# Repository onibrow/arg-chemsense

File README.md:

# Arias Reesearch Group - Chemical Sensors

Quad Channel Differential Potentiometric Sensor

Using the MCP3424 to sense differential voltage - firmware library [here](https://github.com/battosai30/MCP3424)

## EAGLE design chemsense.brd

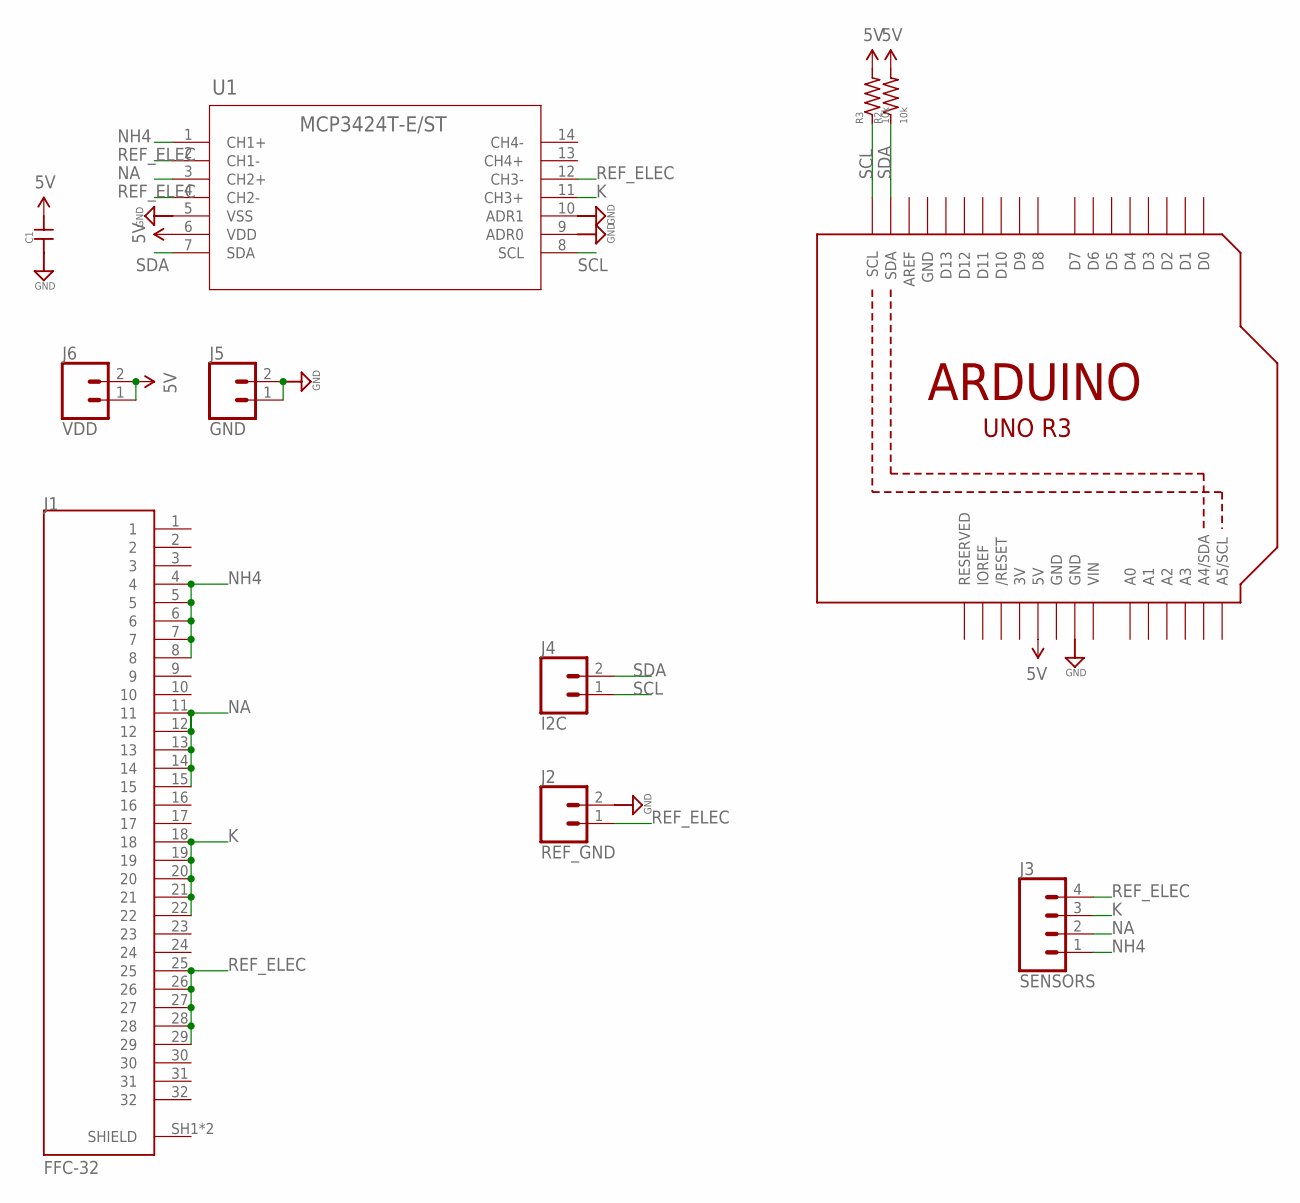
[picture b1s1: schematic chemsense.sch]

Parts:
C1: CAP0603-CAP; 0603-CAP
J1: FFC-32; MOLEX_503480-3200
J2: REF_GND; 1X02
J3: SENSORS; 1X04
J4: I2C; 1X02
J5: GND; 1X02
J6: VDD; 1X02
M1: ARDUINO_R3_ICSP; ARDUINOR3_ICSP
R2, R3: 10k; 0603-RES
U1: MCP3424T-E/ST; TSSOP14_MC

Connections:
3V: M1.3V
5V: C1.2, J6.1, J6.2, M1.5V, R2.2, R3.2, U1.6 (VDD)
GND: C1.1, J2.2, J5.1, J5.2, M1.GND, M1.GND@1 (GND), M1.GND@2 (GND), U1.5 (VSS), U1.9 (ADR0), U1.10 (ADR1)
K: J1.18, J1.19, J1.20, J1.21, J1.22, J3.3, U1.11 (CH3+)
NA: J1.11, J1.12, J1.13, J1.14, J1.15, J3.2, U1.3 (CH2+)
NH4: J1.4, J1.5, J1.6, J1.7, J1.8, J3.1, U1.1 (CH1+)
REF_ELEC: J1.25, J1.26, J1.27, J1.28, J1.29, J2.1, J3.4, U1.2 (CH1-), U1.4 (CH2-), U1.12 (CH3-)
SCL: J4.1, M1.SCL, R3.1, U1.8 (SCL)
SDA: J4.2, M1.SDA, R2.1, U1.7 (SDA)
VIN: M1.VIN

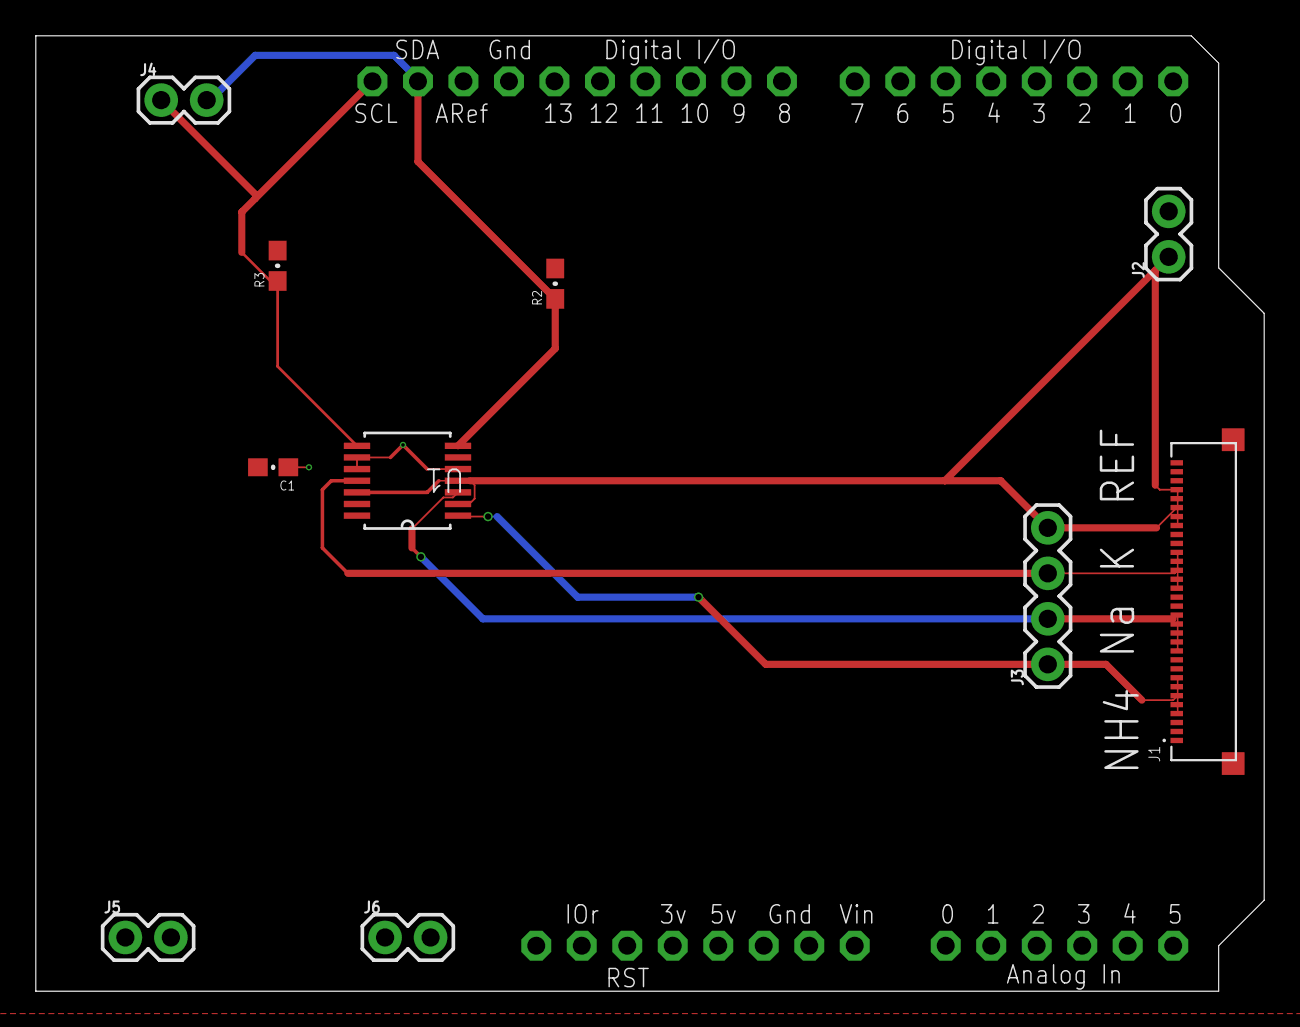
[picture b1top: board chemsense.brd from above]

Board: 2 copper layers, 68.6 x 53.3 mm, 11 parts (0 on the bottom side), 8 nets.

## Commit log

2019-11-07 Initialize repo
2019-11-07 First rendition of board form factor
2019-11-21 add shrots for ref to gnd and electrodes
2020-01-28 first board out and tested with diff firmware
2020-01-29 get pyserial to work and request adc data
2020-02-01 Finish logging data script
2020-02-04 add more parameters
2020-03-13 clean up
2020-07-25 update for shipment
2020-08-05 Fix for windows release
